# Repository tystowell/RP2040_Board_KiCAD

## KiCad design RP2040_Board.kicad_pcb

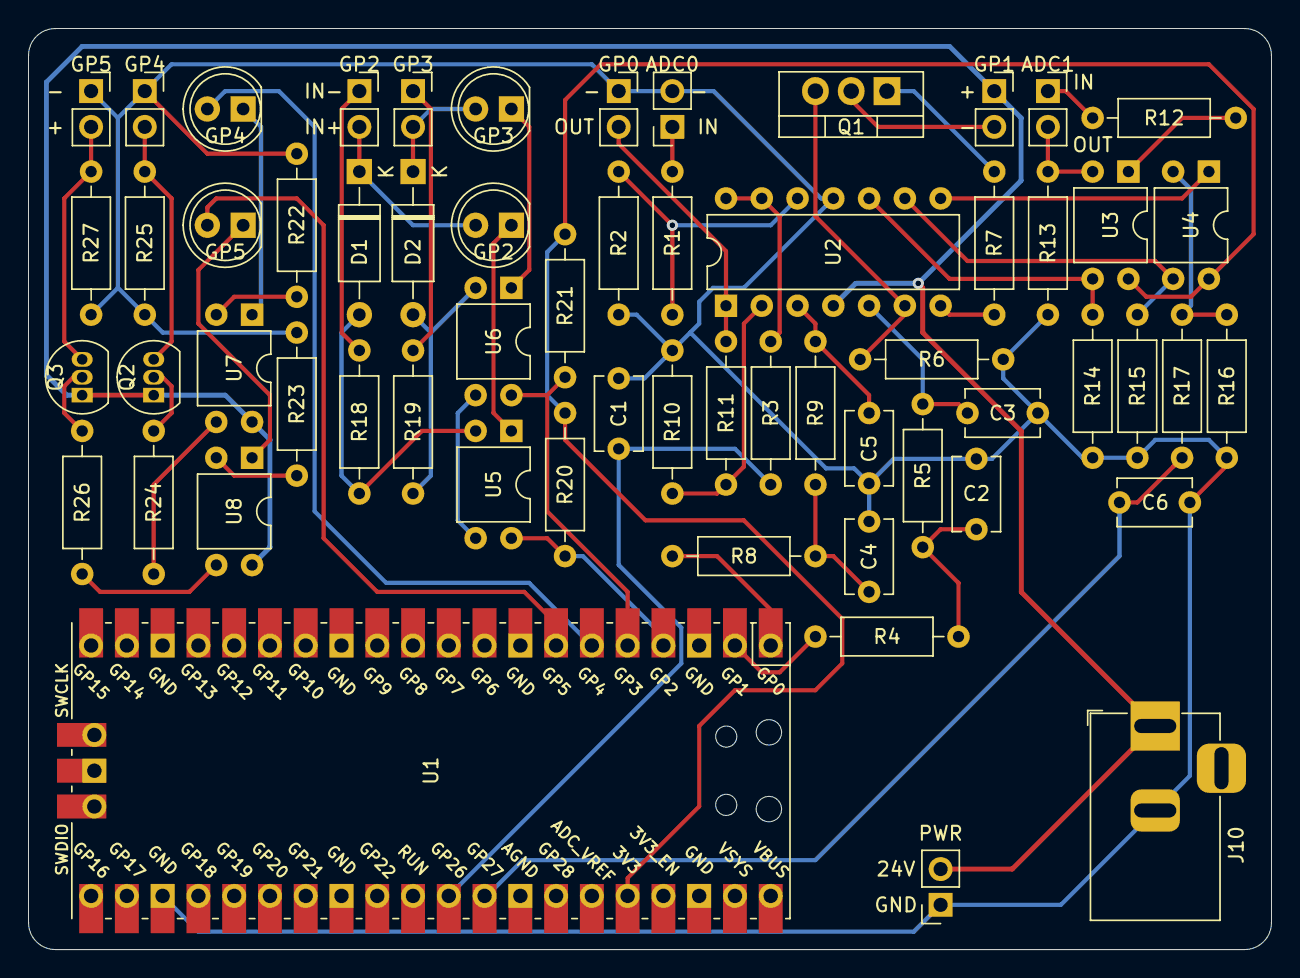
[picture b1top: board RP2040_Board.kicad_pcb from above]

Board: 2 copper layers, 88.3 x 65.4 mm, 60 parts (0 on the bottom side), 49 nets.

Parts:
ADC0: V_IN; PinSocket_1x02_P2.54mm_Vertical
ADC1: mA_IN; PinSocket_1x02_P2.54mm_Vertical
C1: .47μ; C_Disc_D5.1mm_W3.2mm_P5.00mm
C2, C3, C4, C5: 2.2μ; C_Disc_D5.1mm_W3.2mm_P5.00mm
C6: 2.2µ; C_Disc_D5.1mm_W3.2mm_P5.00mm
D1, D2: D; D_A-405_P10.16mm_Horizontal
GP0: V_OUT; PinSocket_1x02_P2.54mm_Vertical
GP1: mA_OUT; PinSocket_1x02_P2.54mm_Vertical
GP2, GP3: DIG_IN; PinSocket_1x02_P2.54mm_Vertical
GP2#2, GP3#2, GP4#2, GP5#2: LED; LED_D5.0mm
GP4, GP5: DIG_OUT; PinSocket_1x02_P2.54mm_Vertical
J10: 24V DC Power; BarrelJack_Horizontal
PWR: GND-24V; PinSocket_1x02_P2.54mm_Vertical
Q1: IRF510N; TO-220-3_Vertical
Q2, Q3: BC337; TO-92_Inline
R1, R11: 22k; R_Axial_DIN0207_L6.3mm_D2.5mm_P10.16mm_Horizontal
R2, R10: 10k; R_Axial_DIN0207_L6.3mm_D2.5mm_P10.16mm_Horizontal
R3, R4, R5, R8, R9, R17: 2.2k; R_Axial_DIN0207_L6.3mm_D2.5mm_P10.16mm_Horizontal
R6, R12, R16: 150; R_Axial_DIN0207_L6.3mm_D2.5mm_P10.16mm_Horizontal
R7: 10; R_Axial_DIN0207_L6.3mm_D2.5mm_P10.16mm_Horizontal
R13: 1M; R_Axial_DIN0207_L6.3mm_D2.5mm_P10.16mm_Horizontal
R14, R15: 47; R_Axial_DIN0207_L6.3mm_D2.5mm_P10.16mm_Horizontal
R18, R19, R25, R27: 4.7k; R_Axial_DIN0207_L6.3mm_D2.5mm_P10.16mm_Horizontal
R20, R21: 20k; R_Axial_DIN0207_L6.3mm_D2.5mm_P10.16mm_Horizontal
R22, R23, R24, R26: 470; R_Axial_DIN0207_L6.3mm_D2.5mm_P10.16mm_Horizontal
U1: Pico; RPi_Pico_SMD_TH
U2: LM324; DIP-14_W7.62mm
U3, U4, U5, U6, U7, U8: PC817; DIP-4_W7.62mm

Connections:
3.3V: R20.1, R21.1, U1.36, U3.4, U4.4
24V: GP1.1, J10.1, PWR.2, Q2.1, Q3.1, U2.4, U7.4, U8.4
/10V to 3.3V Input/IN: ADC0.1, R1.2
/10V to 3.3V Input/OUT: C1.1, R3.1, U1.31
/20mA to 3.3V Input/C_IN: ADC1.1, R12.2
/20mA to 3.3V Input/C_OUT: ADC1.2, R13.2, U3.2
/20mA to 3.3V Input/OUT: C6.1, R17.1, U1.32
/Digital Input/IN+1: D1.1, GP2.2, GP2#2.2
/Digital Input/IN+2: D2.1, GP3.2, GP3#2.2
/Digital Input/IN-1: GP2.1, R18.1
/Digital Input/IN-2: GP3.1, R19.1
/Digital Input/OUT1: R20.2, U1.4, U5.4
/Digital Input/OUT2: R21.2, U1.5, U6.4
/Digital Output/IN1: GP4#2.2, U1.6
/Digital Output/IN2: GP5#2.2, U1.7
/Digital Output/OUT1: GP4.2, Q2.3, R25.2
/Digital Output/OUT2: GP5.2, Q3.3, R27.2
/PWM to 10V Output/OUT: GP0.2, R11.1, U2.1
/PWM to 10V Output/PWM: R8.2, U1.1
/PWM to 20mA Output/OUT: GP1.2, Q1.2
/PWM to 20mA Output/PWM: R4.2, U1.2
GND: ADC0.2, C1.2, C2.2, C3.2, C4.2, C5.2, C6.2, GP0.1, GP4.1, GP5.1, J10.2, PWR.1, R2.1, R6.2, R10.2, R13.1, R14.1, R15.1, R16.1, R22.1, R23.1, R25.1, R27.1, U1.23, U2.11, U5.3, U6.3
unnamed: C2.1, R4.1, R5.2
unnamed: C3.1, R5.1, U2.5
unnamed: C4.1, R8.1, R9.2
unnamed: C5.1, R9.1, U2.3
unnamed: D1.2, R18.2, U5.2
unnamed: D2.2, R19.2, U6.2
unnamed: GP2#2.1, U5.1
unnamed: GP3#2.1, U6.1
unnamed: GP4#2.1, U7.1
unnamed: GP5#2.1, U8.1
unnamed: Q1.1, R7.1
unnamed: Q1.3, R6.1, U2.6
unnamed: Q2.2, R24.2
unnamed: Q3.2, R26.2
unnamed: R1.1, R2.2, U2.12
unnamed: R3.2, U2.13, U2.14
unnamed: R7.2, U2.7
unnamed: R10.1, R11.2, U2.2
unnamed: R12.1, U3.1
unnamed: R14.2, U2.10, U3.3
unnamed: R15.2, U2.9, U4.3
unnamed: R16.2, R17.2, U4.2
unnamed: R22.2, U7.2
unnamed: R23.2, U8.2
unnamed: R24.1, U7.3
unnamed: R26.1, U8.3
unnamed: U2.8, U4.1

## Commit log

2021-05-20 10V Output Circuit First Revision
2021-05-20 Added a library for the Pi Pico
2021-05-20 10V Input Circuit First Revision
2021-05-24 Added PWM to 20mA Output Subcircuit
2021-05-24 Added 20mA to 3.3V Input Subcircuit
2021-05-24 Op amp power supply in 20mA_IN switched to 5V
2021-05-25 Previous current input circuit was reaching op amp saturation. Possible solution may involve transistor, but for now, higher power supply is sufficient.
2021-05-25 Added Optically Isolated Digital Input
2021-05-25 Comments and Notation for clarity
2021-05-26 Cleanup, added second digital input, and created sheet for digital output (currently empty)
2021-05-26 Testing and adjustments
2021-05-26 Basic Digital Output Circuit (First Revision, UNTESTED)
2021-05-27 Footprint Association
2021-05-27 Fixed a couple of discrepancies between my test circuit and the schematic
2021-05-27 Status LED was ruining the reverse voltage protection LED's purpose
2021-05-31 Finished 1st revision of 24V digital output circuit
2021-05-31 Cleanup and ERC compliance. Probably ready for Pcbnew after footprint association is done.
2021-05-31 Finished component association
2021-05-31 Started PCB board design (TH, V1)
2021-06-02 More PCB design work
2021-06-02 Everything in the PCB is now wired together
2021-06-02 Added a copper pad for ground
2021-06-02 Forgot to add a small trace. Now the board is complete.
2021-06-02 Adjusted 24V traces to be .35mm and recreated fill zone
